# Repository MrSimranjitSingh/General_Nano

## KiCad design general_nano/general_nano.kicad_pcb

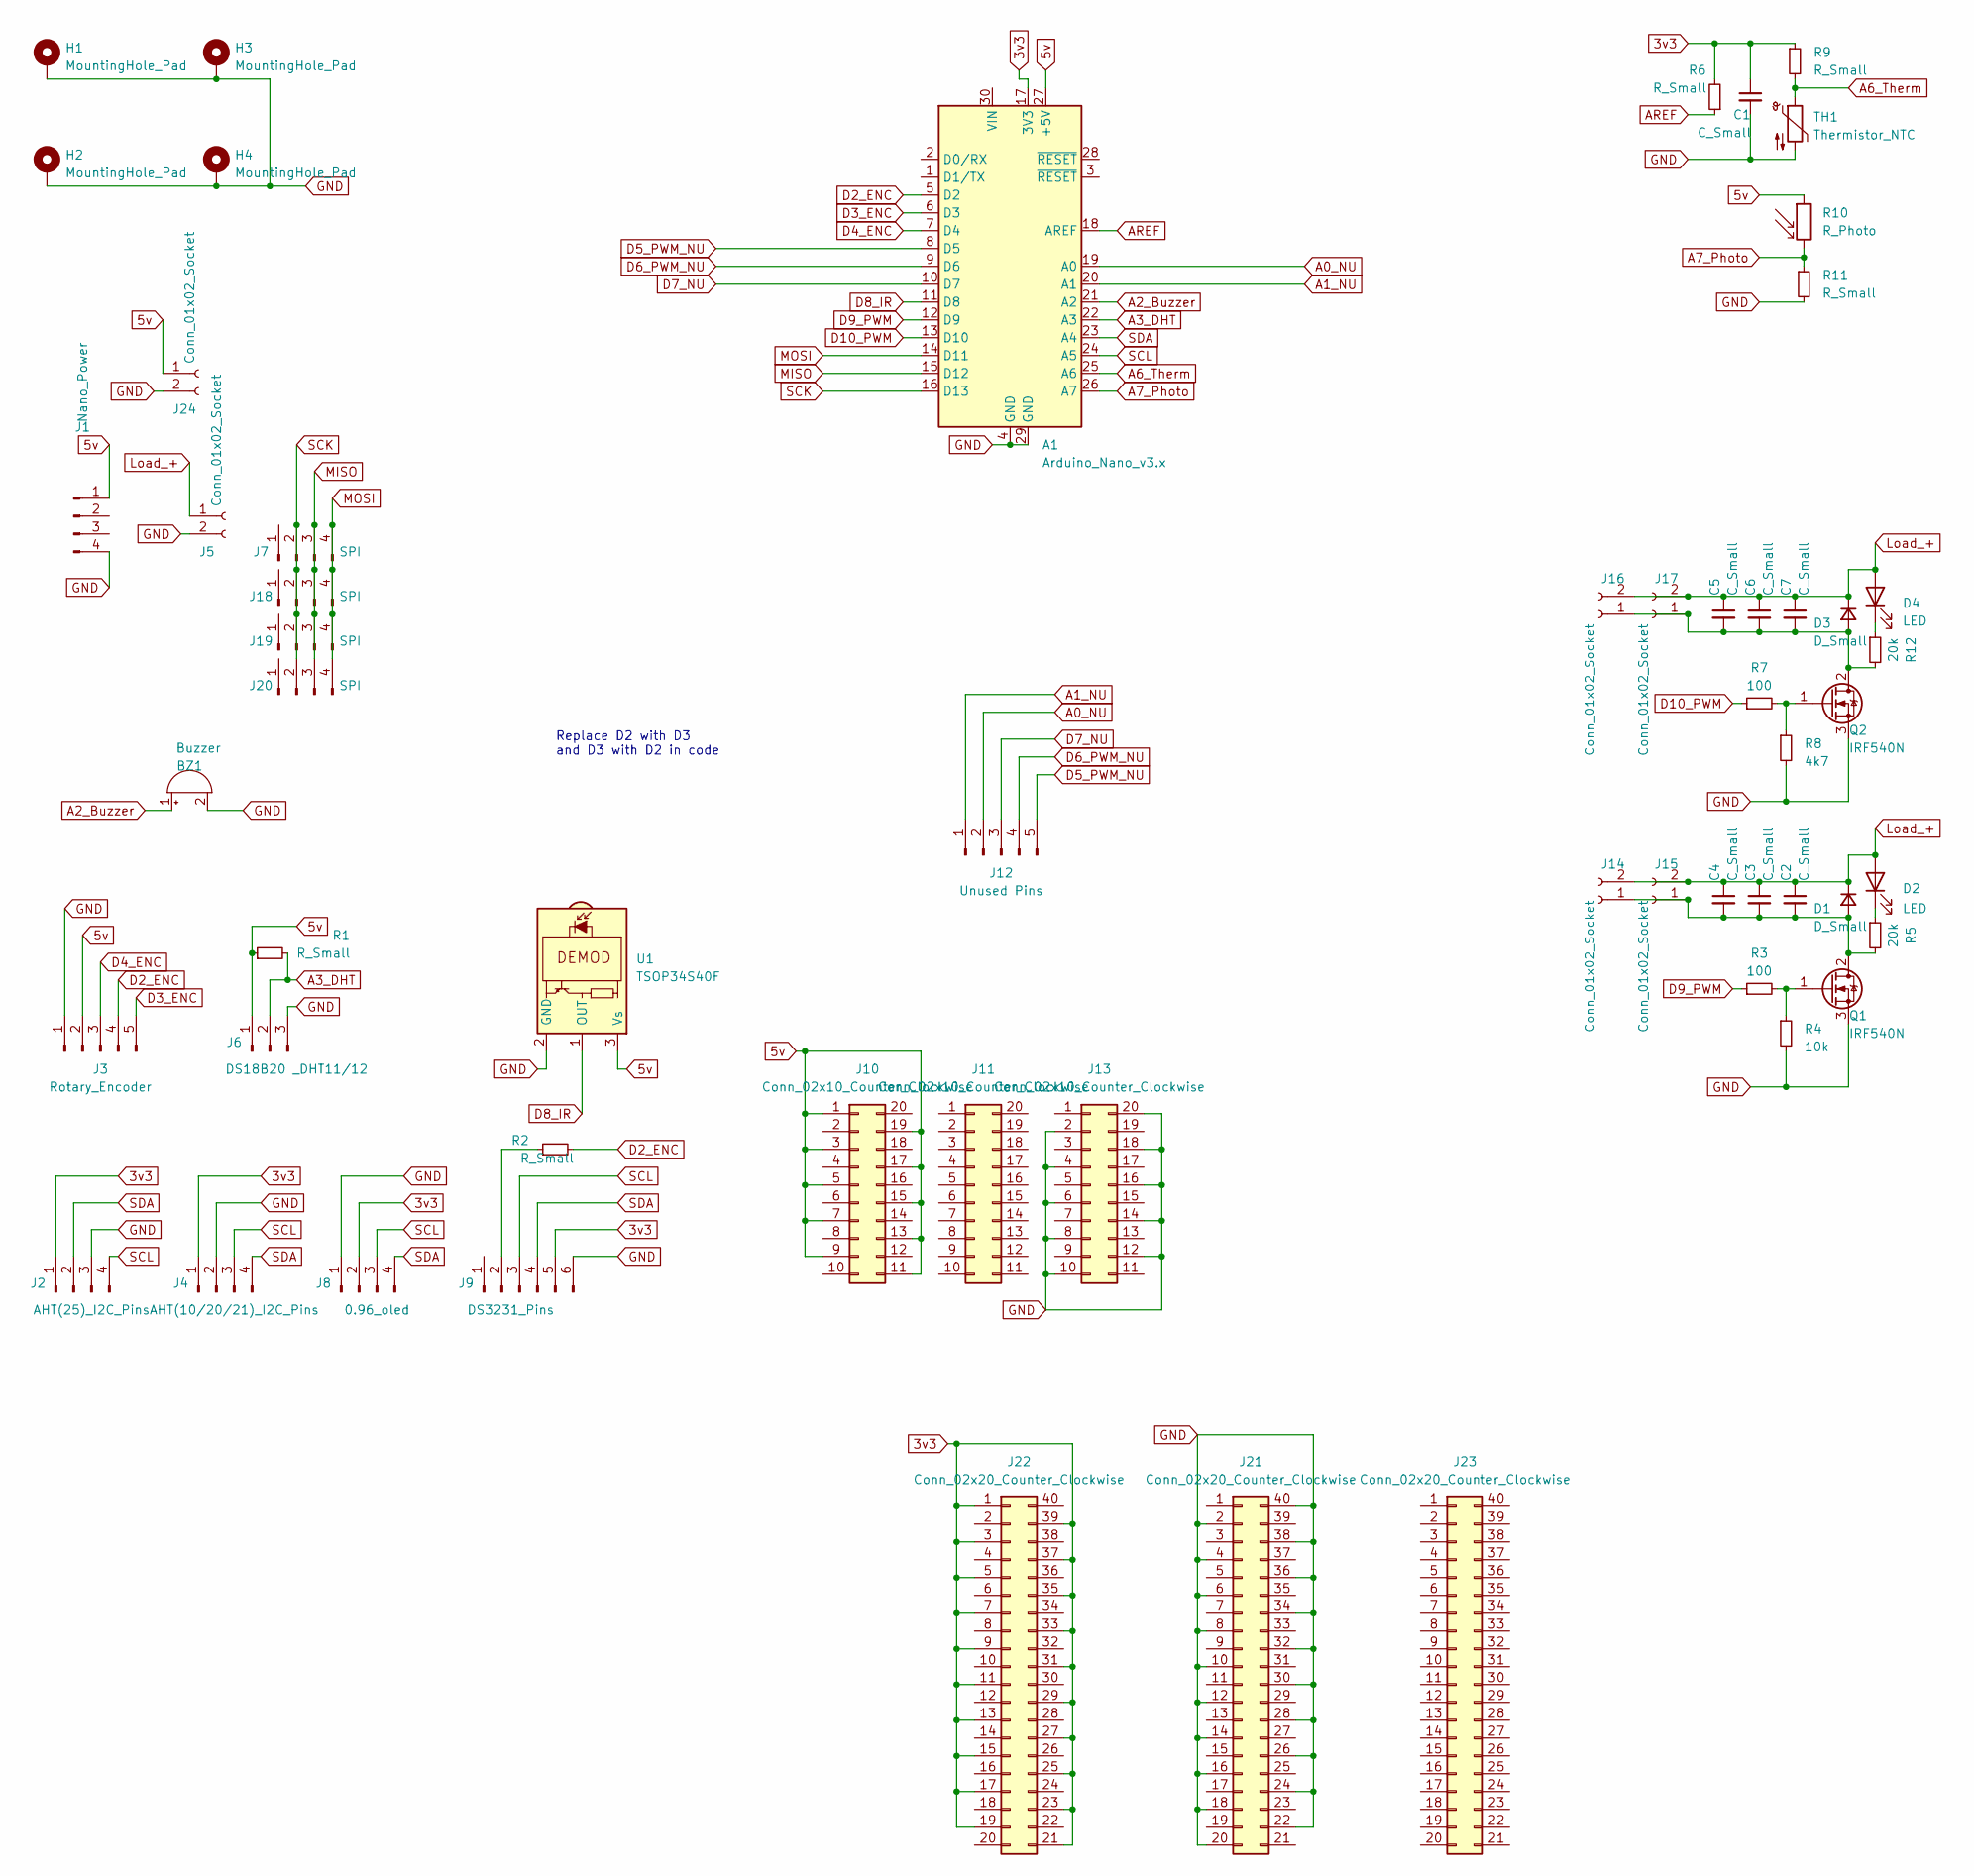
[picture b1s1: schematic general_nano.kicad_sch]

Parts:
A1: Arduino_Nano_v3.x; Arduino_Nano
BZ1: Buzzer; Buzzer_12x9.5RM7.6
C1: C_Small; C_Radial_D4.0mm_H7.0mm_P1.50mm
C2, C3, C4, C5, C6, C7: C_Small; C_1206_3216Metric_Pad1.33x1.80mm_HandSolder
D1, D3: D_Small; D_DO-41_SOD81_P7.62mm_Horizontal
D2, D4: LED; LED_D5.0mm_Clear
H1, H2, H3, H4: MountingHole_Pad; MountingHole_3.2mm_M3_DIN965_Pad_TopBottom
J1: Nano_Power; PinSocket_1x04_P2.54mm_Vertical
J2: AHT(25)_I2C_Pins; PinSocket_1x04_P2.54mm_Vertical
J3: Rotary_Encoder; PinSocket_1x05_P2.54mm_Vertical
J4: AHT(10/20/21)_I2C_Pins; PinSocket_1x04_P2.54mm_Vertical
J5: Conn_01x02_Socket; SolderWire-2.5sqmm_1x02_P8.8mm_D2.4mm_OD4.4mm
J6: DS18B20 _DHT11/12; PinSocket_1x03_P2.54mm_Vertical
J7, J18, J19, J20: SPI; PinSocket_1x04_P2.54mm_Vertical
J8: 0.96_oled; PinSocket_1x04_P2.54mm_Vertical
J9: DS3231_Pins; PinSocket_1x06_P2.54mm_Vertical
J10, J11, J13: Conn_02x10_Counter_Clockwise; PinSocket_2x10_P2.54mm_Vertical
J12: Unused Pins; PinSocket_1x05_P2.54mm_Vertical
J14, J15, J16, J17: Conn_01x02_Socket; SolderWire-1sqmm_1x02_P7.8mm_D1.4mm_OD3.9mm
J21, J22, J23: Conn_02x20_Counter_Clockwise; PinSocket_2x20_P2.54mm_Vertical
J24: Conn_01x02_Socket; SolderWire-1.5sqmm_1x02_P6mm_D1.7mm_OD3mm
Q1, Q2: IRF540N; TO-220-3_Vertical
R1, R9, R11: R_Small; R_Axial_DIN0204_L3.6mm_D1.6mm_P7.62mm_Horizontal
R2, R6: R_Small; R_0815_2038Metric_Pad1.20x4.05mm_HandSolder
R3, R7: 100; R_Axial_DIN0204_L3.6mm_D1.6mm_P7.62mm_Horizontal
R4: 10k; R_Axial_DIN0204_L3.6mm_D1.6mm_P7.62mm_Horizontal
R5, R12: 20k; R_Axial_DIN0204_L3.6mm_D1.6mm_P7.62mm_Horizontal
R8: 4k7; R_Axial_DIN0204_L3.6mm_D1.6mm_P7.62mm_Horizontal
R10: R_Photo; R_LDR_5.1x4.3mm_P3.4mm_Vertical
TH1: Thermistor_NTC; R_Axial_DIN0204_L3.6mm_D1.6mm_P7.62mm_Horizontal
U1: TSOP34S40F; Vishay_MOLD-3Pin

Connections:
3v3: A1.17 (3V3), C1.1, J2.1, J4.1, J8.2, J9.5, J22.1, J22.3, J22.5, J22.7, J22.9, J22.11, J22.13, J22.15, J22.17, J22.19, J22.21, J22.23, J22.25, J22.27, J22.29, J22.31, J22.33, J22.35, J22.37, J22.39, R6.2, R9.1
5v: A1.27 (+5V), J1.1, J3.2, J6.1, J10.1, J10.3, J10.5, J10.7, J10.9, J10.11, J10.13, J10.15, J10.17, J10.19, J24.1, R1.1, R10.1, U1.3 (Vs)
A0_NU: A1.19 (A0), J12.2
A1_NU: A1.20 (A1), J12.1
A2_Buzzer: A1.21 (A2), BZ1.1 (-)
A3_DHT: A1.22 (A3), J6.2, R1.2
A6_Therm: A1.25 (A6), R9.2, TH1.1
A7_Photo: A1.26 (A7), R10.2, R11.1
AREF: A1.18 (AREF), R6.1
D2_ENC: A1.5 (D2), J3.4, R2.2
D3_ENC: A1.6 (D3), J3.5
D4_ENC: A1.7 (D4), J3.3
D5_PWM_NU: A1.8 (D5), J12.5
D6_PWM_NU: A1.9 (D6), J12.4
D7_NU: A1.10 (D7), J12.3
D8_IR: A1.11 (D8), U1.1 (OUT)
D9_PWM: A1.12 (D9), R3.1
D10_PWM: A1.13 (D10), R7.1
GND: A1.4 (GND), A1.29 (GND), BZ1.2 (+), C1.2, H1.1, H2.1, H3.1, H4.1, J1.4, J2.3, J3.1, J4.2, J5.2, J6.3, J8.1, J9.6, J13.2, J13.4, J13.6, J13.8, J13.10, J13.12, J13.14, J13.16, J13.18, J13.20, J21.2, J21.4, J21.6, J21.8, J21.10, J21.12, J21.14, J21.16, J21.18, J21.20, J21.22, J21.24, J21.26, J21.28, J21.30, J21.32, J21.34, J21.36, J21.38, J21.40, J24.2, Q1.3 (S), Q2.3 (S), R4.2, R8.2, R11.2, TH1.2, U1.2 (GND)
Load_+: C2.1, C3.1, C4.1, C5.1, C6.1, C7.1, D1.1 (K), D2.2 (A), D3.1 (K), D4.2 (A), J5.1, J14.2, J15.2, J16.2, J17.2
MISO: A1.15 (D12), J7.3, J18.3, J19.3, J20.3
MOSI: A1.14 (D11), J7.4, J18.4, J19.4, J20.4
unnamed: C2.2, C3.2, C4.2, D1.2 (A), J14.1, J15.1, Q1.2 (D), R5.2
unnamed: D2.1 (K), R5.1
unnamed: C5.2, C6.2, C7.2, D3.2 (A), J16.1, J17.1, Q2.2 (D), R12.2
unnamed: D4.1 (K), R12.1
unnamed: J9.2, R2.1
unnamed: Q1.1 (G), R3.2, R4.1
unnamed: Q2.1 (G), R7.2, R8.1
SCK: A1.16 (D13), J7.2, J18.2, J19.2, J20.2
SCL: A1.24 (A5), J2.4, J4.3, J8.3, J9.3
SDA: A1.23 (A4), J2.2, J4.4, J8.4, J9.4

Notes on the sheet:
Replace D2 with D3 and D3 with D2 in code

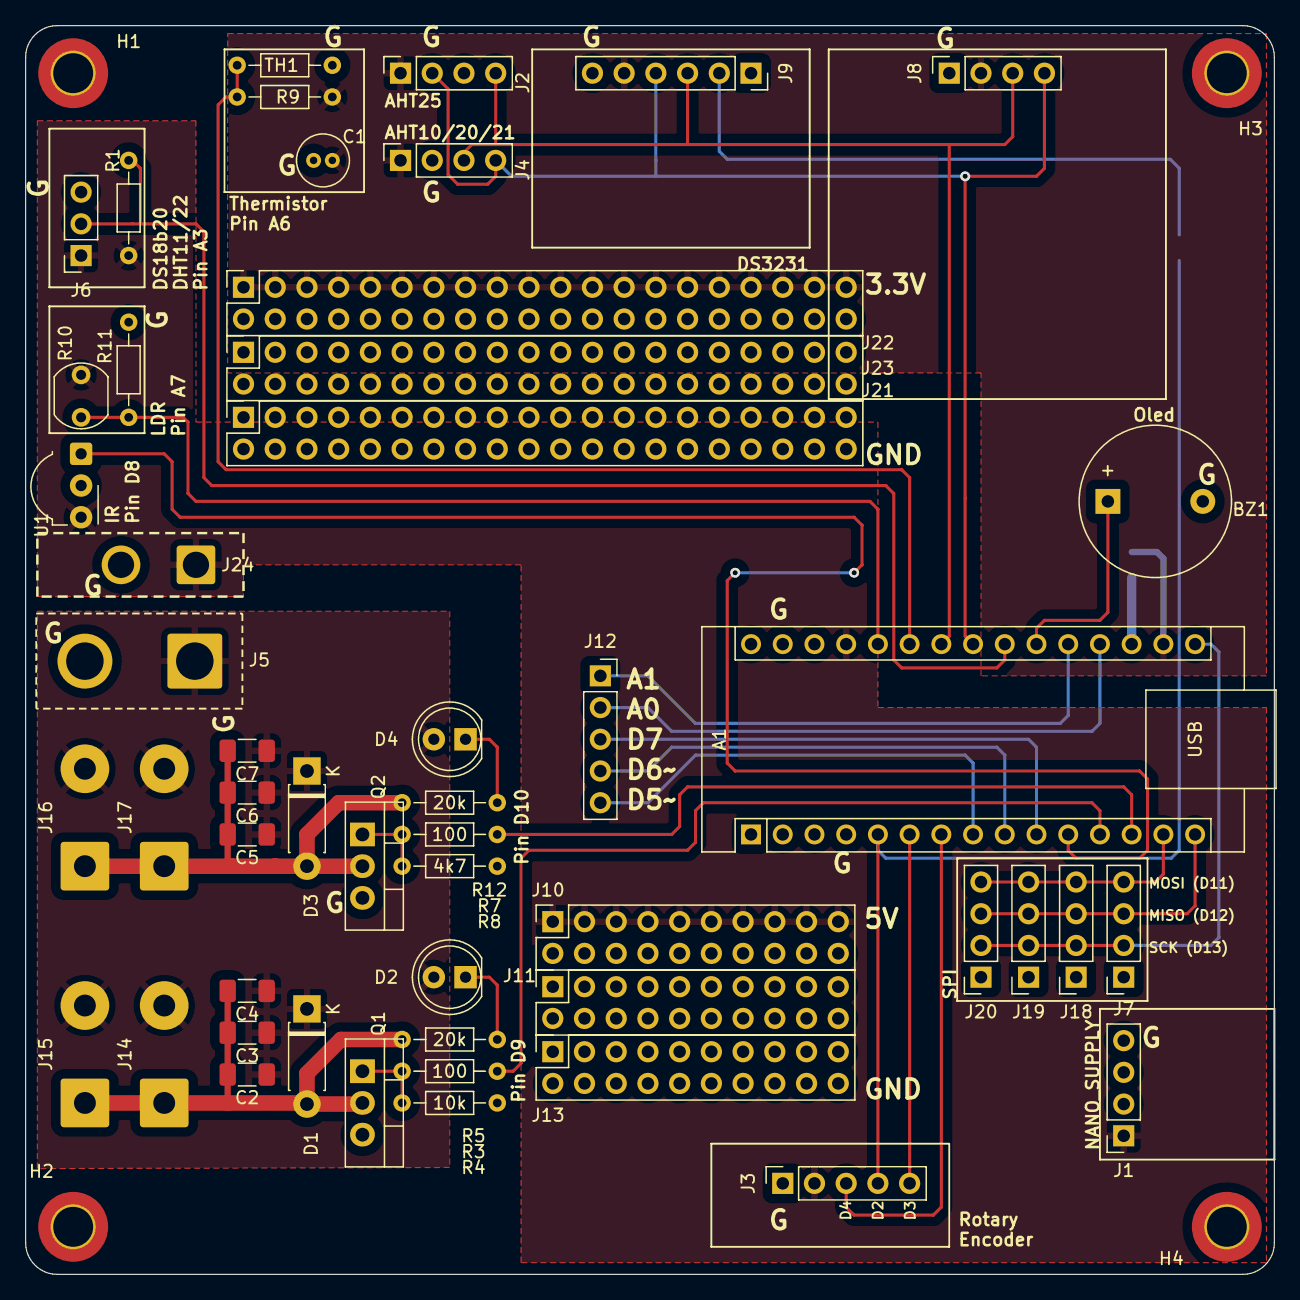
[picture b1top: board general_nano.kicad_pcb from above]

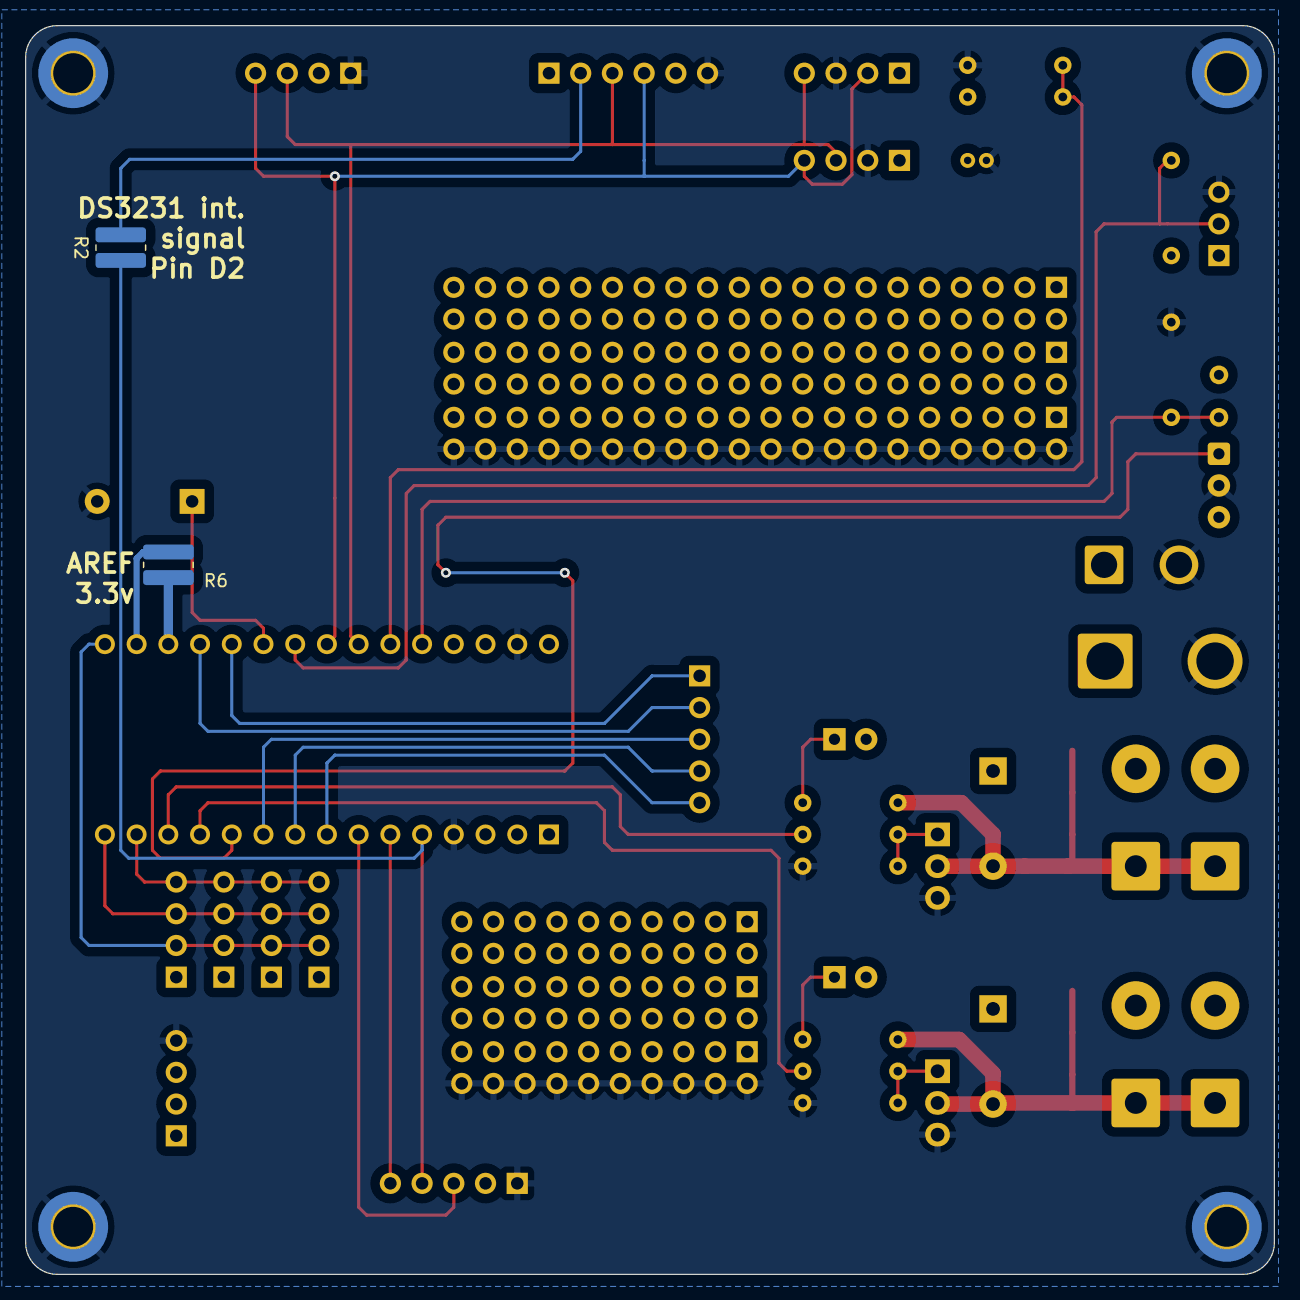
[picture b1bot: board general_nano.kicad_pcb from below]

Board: 2 copper layers, 100.0 x 100.0 mm, 57 parts (2 on the bottom side), 32 nets.
